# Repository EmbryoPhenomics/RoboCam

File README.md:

# RoboCam

## Robotic instrument for timelapse imaging in multiwell plate format

RoboCam is a compact, modular laboratory instrument, with robotic motion and built-in compute, it is capable of timelapse imaging of various multiwell plate formats. 

Some of the key specifications of this instruments are as follows:

| Component | Description |
|:---|:---|
| Robotic stage | Automated lead-screw driven XYZ stage with < 1 µm precision and < 10 µm repeatability. The stage is camera-driven rather than sample-driven, reducing vibration transmitted to samples. |
| Processors | Raspberry Pi 5 8Gb RAM computer with built-in fast NVME storage running Debian Linux. |
| Camera sensor | Two camera sensor options: Global shutter CMOS 1.58-megapixel (Sony IMX296LQR-C). Rolling shutter CMOS 12.3-megapixel (Sony IMX477R) |
| Video resolution | Global shutter: 1456x1088 60fps max. Rolling shutter: 1920x1080 50fps max. Higher resolution possible at reduced framerate. Resolution and framerate can be configured using built-in app. |
| Lens | Adjustable high magnification and low magnification lens included. Auxillary, stackable lenses (x2, x3, x4 and x6) provided for high magnification lens to achieve greater magnification. | 
| Lighting | Ring light consisting of 36 individually lit 3mm LEDs. Brightness can be configured and controlled through built-in app. |
| Configuration | Setup via Web App using built-in touchscreen, enabling live stream and config of camera sensor, positioning of XYZ stage and programming of experimental schedule. Experimental data can be captured to built-in disk or to USB attached storage. |
| Sensors | Compact, enclosed aluminium frame with damped door for access and panel cutouts for routing of auxiliary hardware. | 
| Dimensions | 325 mm x 442 mm x 510 mm |

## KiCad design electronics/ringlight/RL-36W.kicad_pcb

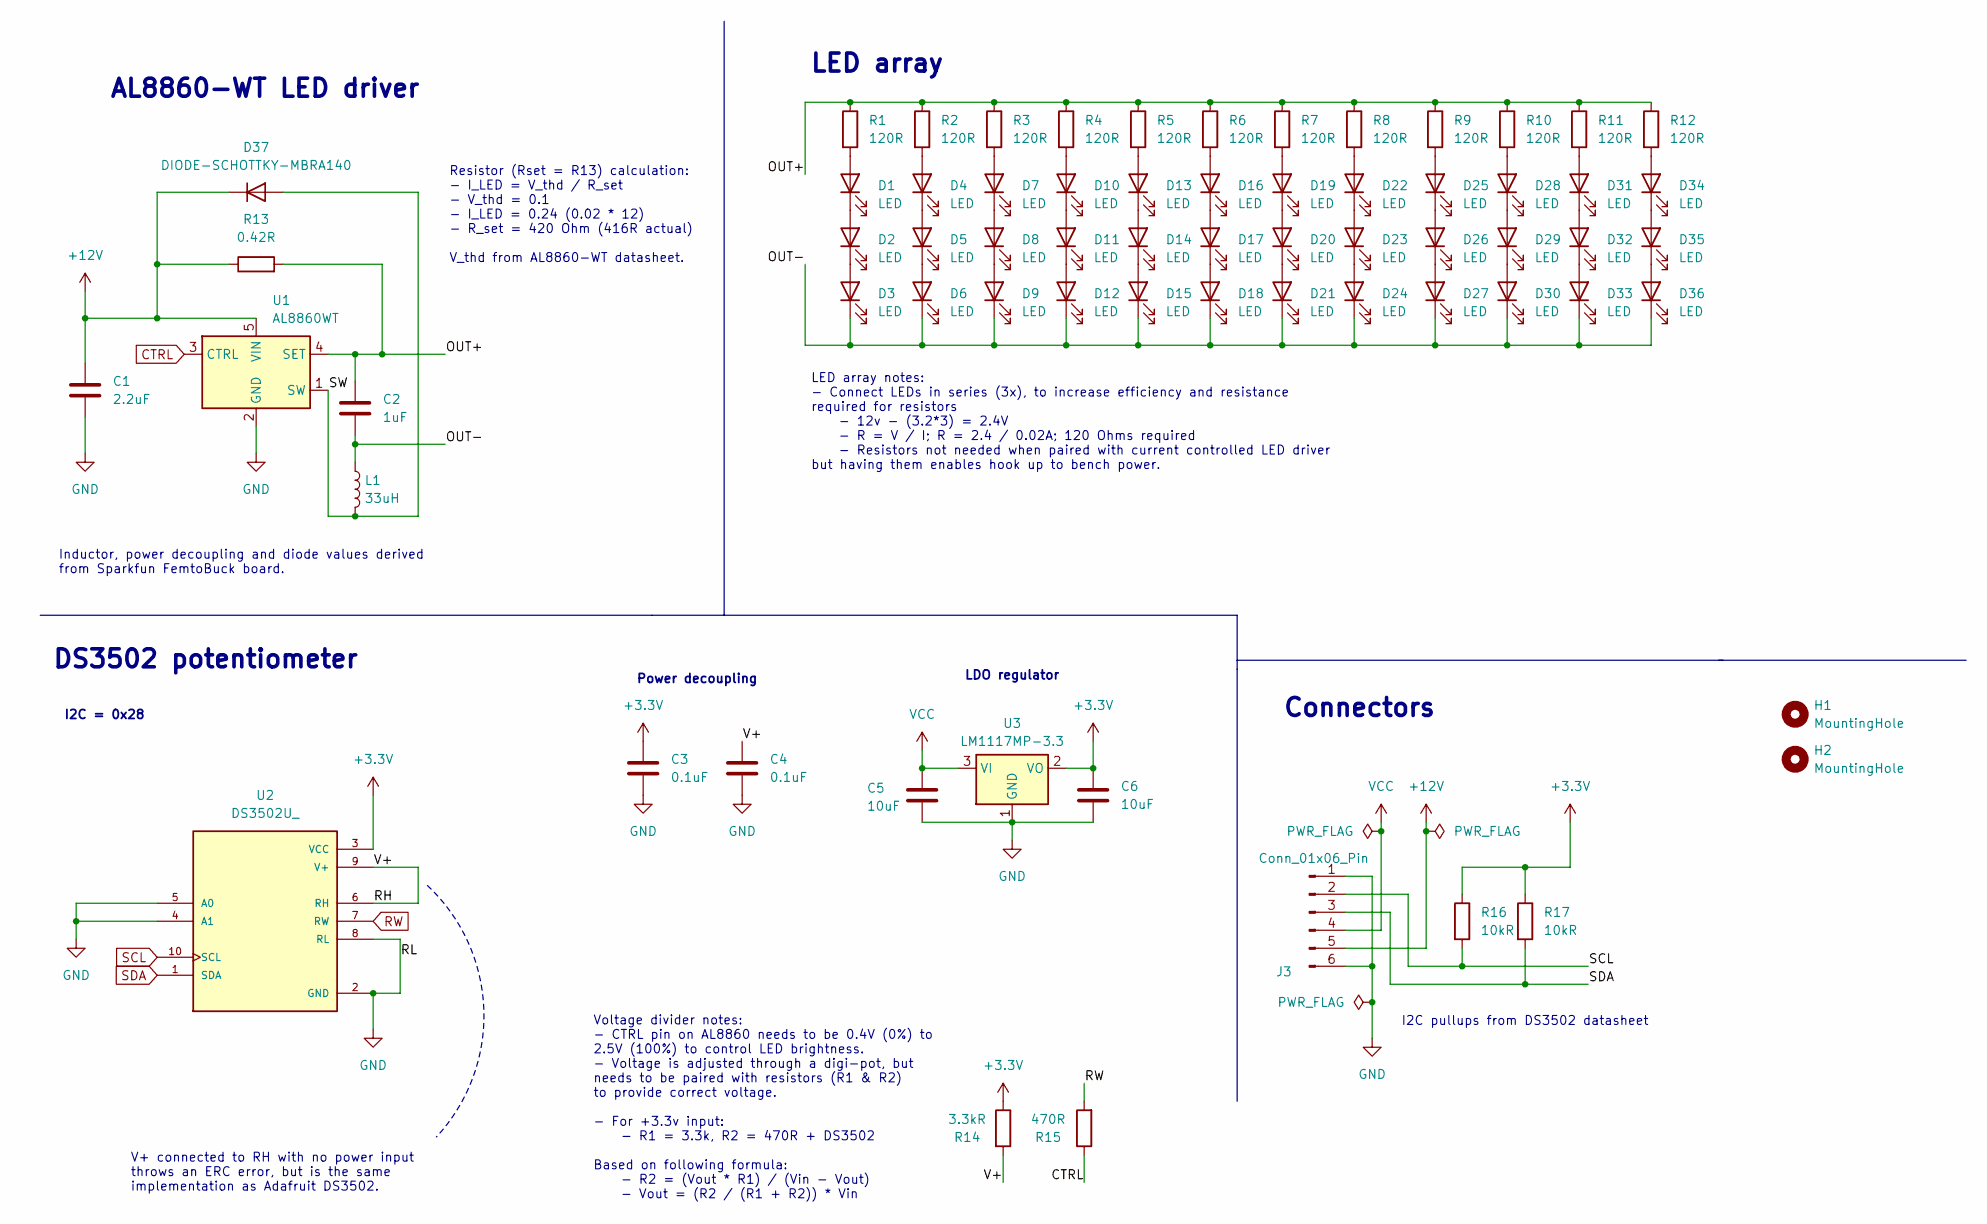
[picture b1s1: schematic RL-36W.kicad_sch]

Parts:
C1: 2.2uF; C_1206_3216Metric
C2: 1uF; C_1206_3216Metric
C3, C4: 0.1uF; C_0402_1005Metric
C5, C6: 10uF; C_1206_3216Metric
D1, D2, D3, D4, D5, D6, D7, D8, D9, D10, D11, D12, D13, D14, D15, D16, D17, D18, D19, D20, D21, D22, D23, D24, D25, D26, D27, D28, D29, D30, D31, D32, D33, D34, D35, D36: LED; LED_D3.0mm_2
D37: DIODE-SCHOTTKY-MBRA140; D_SMA
H1, H2: MountingHole; MountingHole_2mm
J3: Conn_01x06_Pin; JST_PH_S6B-PH-K_1x06_P2.00mm_Horizontal
L1: 33uH; L_Bourns_SRN6045TA
R1, R2, R3, R4, R5, R6, R7, R8, R9, R10, R11, R12: 120R; R_0402_1005Metric
R13: 0.42R; R_0603_1608Metric
R14: 3.3kR; R_0603_1608Metric
R15: 470R; R_0402_1005Metric
R16, R17: 10kR; R_0603_1608Metric
U1: AL8860WT; TSOT-23-5
U2: DS3502U_; SOP50P490X110-10N; PARTREV 1
U3: LM1117MP-3.3; SOT-223-3_TabPin2

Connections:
+3.3V: C3.1, C6.1, R14.1, R16.1, R17.1, U2.3 (VCC), U3.2 (VO)
+12V: C1.1, D37.1 (K), J3.5, R13.1, U1.5 (VIN)
/OUT+: C2.1, R1.1, R2.1, R3.1, R4.1, R5.1, R6.1, R7.1, R8.1, R9.1, R10.1, R11.1, R12.1, R13.2, U1.4 (SET)
/OUT-: C2.2, D3.1 (K), D6.1 (K), D9.1 (K), D12.1 (K), D15.1 (K), D18.1 (K), D21.1 (K), D24.1 (K), D27.1 (K), D30.1 (K), D33.1 (K), D36.1 (K), L1.1
/RH: C4.1, R14.2, U2.6 (RH), U2.9 (V+)
/SW: D37.2 (A), L1.2, U1.1 (SW)
CTRL: R15.1, U1.3 (CTRL)
GND: C1.2, C3.2, C4.2, C5.2, C6.2, J3.1, J3.6, U1.2 (GND), U2.2 (GND), U2.4 (A1), U2.5 (A0), U2.8 (RL), U3.1 (GND)
unnamed: D1.2 (A), R1.2
unnamed: D1.1 (K), D2.2 (A)
unnamed: D2.1 (K), D3.2 (A)
unnamed: D4.2 (A), R2.2
unnamed: D4.1 (K), D5.2 (A)
unnamed: D5.1 (K), D6.2 (A)
unnamed: D7.2 (A), R3.2
unnamed: D7.1 (K), D8.2 (A)
unnamed: D8.1 (K), D9.2 (A)
unnamed: D10.2 (A), R4.2
unnamed: D10.1 (K), D11.2 (A)
unnamed: D11.1 (K), D12.2 (A)
unnamed: D13.2 (A), R5.2
unnamed: D13.1 (K), D14.2 (A)
unnamed: D14.1 (K), D15.2 (A)
unnamed: D16.2 (A), R6.2
unnamed: D16.1 (K), D17.2 (A)
unnamed: D17.1 (K), D18.2 (A)
unnamed: D19.2 (A), R7.2
unnamed: D19.1 (K), D20.2 (A)
unnamed: D20.1 (K), D21.2 (A)
unnamed: D22.2 (A), R8.2
unnamed: D22.1 (K), D23.2 (A)
unnamed: D23.1 (K), D24.2 (A)
unnamed: D25.2 (A), R9.2
unnamed: D25.1 (K), D26.2 (A)
unnamed: D26.1 (K), D27.2 (A)
unnamed: D28.2 (A), R10.2
unnamed: D28.1 (K), D29.2 (A)
unnamed: D29.1 (K), D30.2 (A)
unnamed: D31.2 (A), R11.2
unnamed: D31.1 (K), D32.2 (A)
unnamed: D32.1 (K), D33.2 (A)
unnamed: D34.2 (A), R12.2
unnamed: D34.1 (K), D35.2 (A)
unnamed: D35.1 (K), D36.2 (A)
RW: R15.2, U2.7 (RW)
SCL: J3.2, R16.2, U2.10 (SCL)
SDA: J3.3, R17.2, U2.1 (SDA)
VCC: C5.1, J3.4, U3.3 (VI)

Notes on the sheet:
V+ connected to RH with no power input throws an ERC error, but is the same implementation as Adafruit DS3502.
I2C = 0x28
LED array notes: - Connect LEDs in series (3x), to increase efficiency and resistance required for resistors - 12v - (3.2*3) = 2.4V - R = V / I; R = 2.4 / 0.02A; 120 Ohms required - Resistors not needed when paired with current controlled LED driver but having them enables hook up to bench power.
Connectors
LED array
Resistor (Rset = R13) calculation: - I_LED = V_thd / R_set - V_thd = 0.1 - I_LED = 0.24 (0.02 * 12) - R_set = 420 Ohm (416R actual) V_thd from AL8860-WT datasheet.
Power decoupling
Inductor, power decoupling and diode values derived from Sparkfun FemtoBuck board.
DS3502 potentiometer
Voltage divider notes: - CTRL pin on AL8860 needs to be 0.4V (0%) to 2.5V (100%) to control LED brightness. - Voltage is adjusted through a digi-pot, but needs to be paired with resistors (R1 & R2) to provide correct voltage. - For +3.3v input: - R1 = 3.3k, R2 = 470R + DS3502 Based on following for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
LDO regulator
AL8860-WT LED driver
I2C pullups from DS3502 datasheet

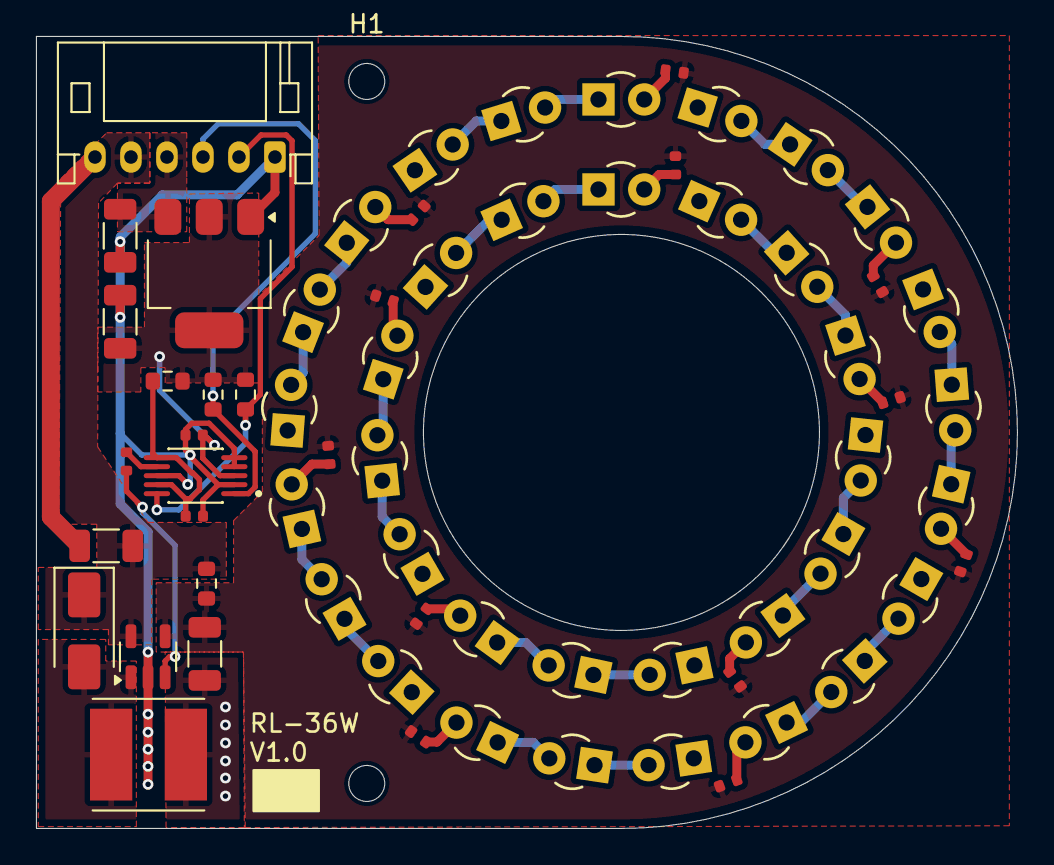
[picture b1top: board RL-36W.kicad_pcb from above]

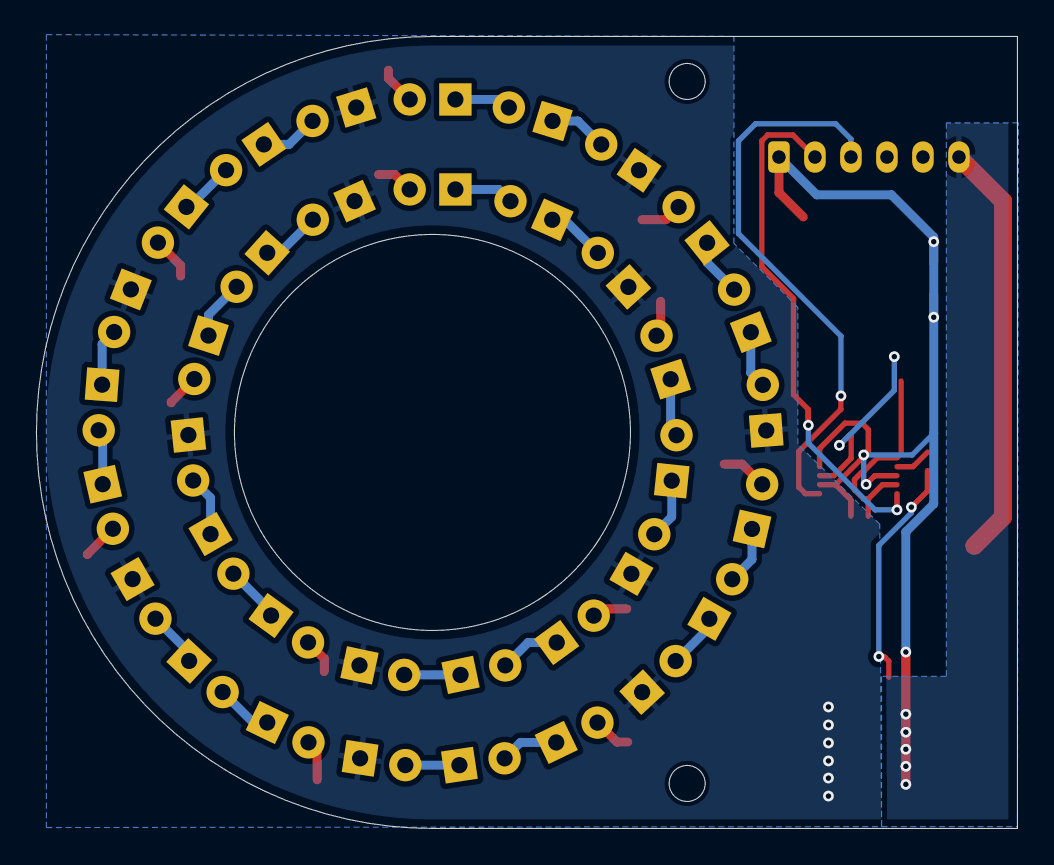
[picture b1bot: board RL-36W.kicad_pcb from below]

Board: 2 copper layers, 54.5 x 44.0 mm, 67 parts (36 on the bottom side), 48 nets.

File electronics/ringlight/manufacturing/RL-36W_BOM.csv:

Comment,Designator,Footprint,JLCPCB Part #,Notes,Correct?
2.2uF,C1,Capacitor_SMD:C_1206_3216Metric,C472849,,
1uF,C2,Capacitor_SMD:C_1206_3216Metric,C577248,,
0.1uF,"C3,C4",Capacitor_SMD:C_0402_1005Metric,C307331,,
10uF,"C5,C6",Capacitor_SMD:C_1206_3216Metric,C5141283,,
DIODE-SCHOTTKY-MBRA140,D37,Diode_SMD:D_SMA,C54798,,
33uH,L1,Inductor_SMD:L_Bourns_SRN6045TA,C780211,,
120R,"R1,R2,R3,R4,R5,R6,R7,R8,R9,R10,R11,R12",attempt_2:R_0402_1005Metric,C911631,,
0.42R,R13,Resistor_SMD:R_0603_1608Metric,C705494,,
3.3kR,R14,Resistor_SMD:R_0603_1608Metric,C5250825,,
470R,R15,Resistor_SMD:R_0402_1005Metric,C2689463,,
10kR,"R16,R17",Resistor_SMD:R_0603_1608Metric,C99198,,
AL8860WT,U1,Package_TO_SOT_SMD:TSOT-23-5,C125330,,
DS3502U_,U2,attempt_2:SOP50P490X110-10N,C2649363,,
LM1117MP-3.3,U3,Package_TO_SOT_SMD:SOT-223-3_TabPin2,C9662,,

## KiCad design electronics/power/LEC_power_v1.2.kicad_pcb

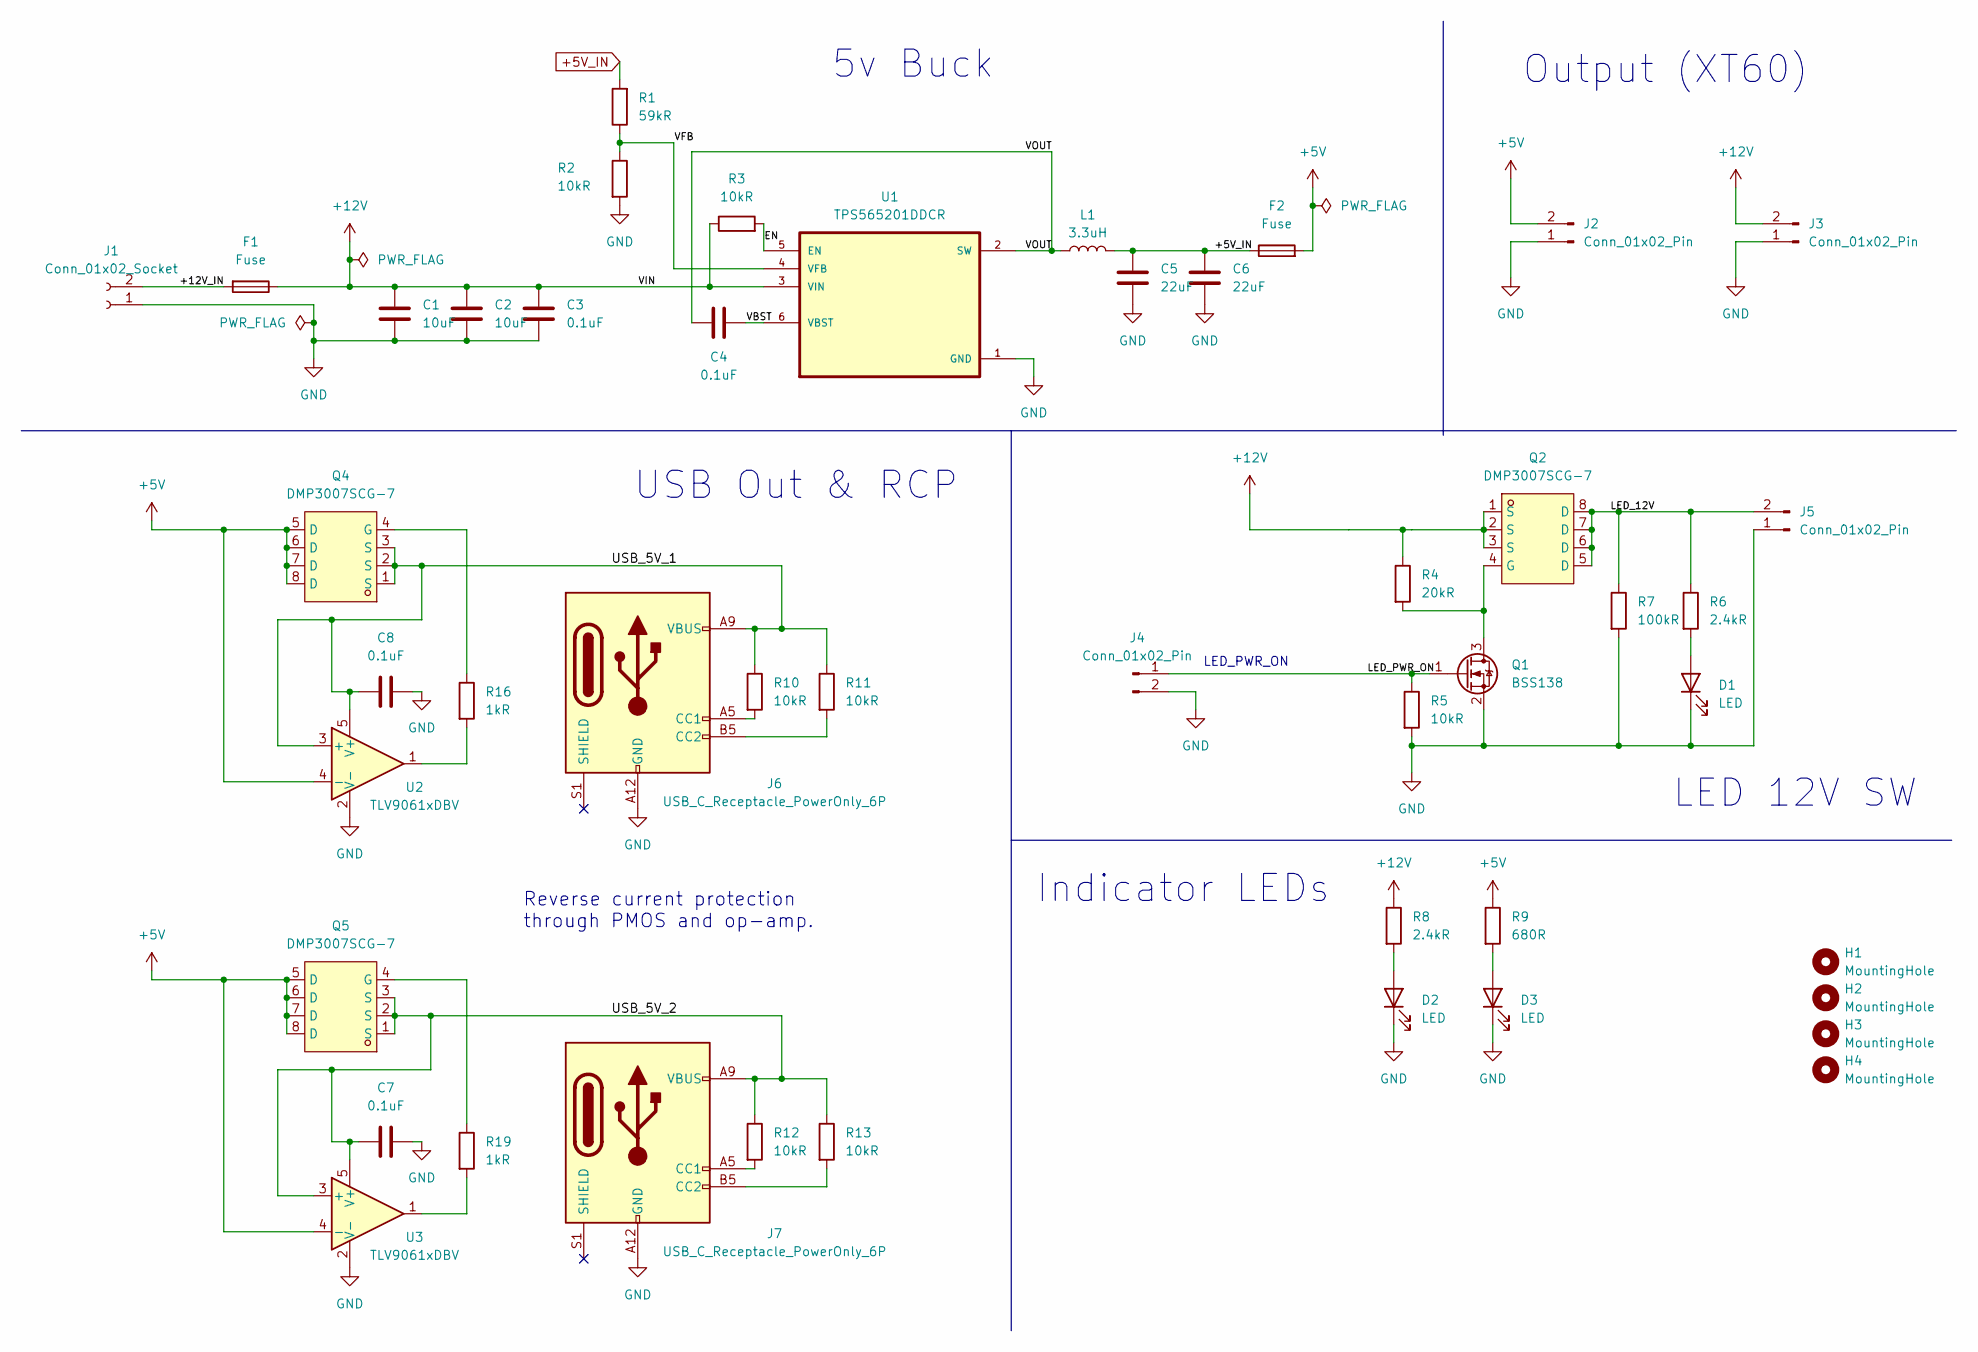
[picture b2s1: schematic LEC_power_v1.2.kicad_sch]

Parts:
C1, C2: 10uF; C_0805_2012Metric
C3, C4, C7, C8: 0.1uF; C_0603_1608Metric
C5, C6: 22uF; C_1206_3216Metric
D1, D2, D3: LED; LED_0603_1608Metric
F1, F2: Fuse; CamdenBoss_FuseHolder_5x20mm
H1, H2, H3, H4: MountingHole; MountingHole_3.2mm_M3
J1: Conn_01x02_Socket; AMASS_XT60PW-M_1x02_P7.20mm_Horizontal
J2, J3: Conn_01x02_Pin; AMASS_XT60PW-F_1x02_P7.20mm_Horizontal
J4: Conn_01x02_Pin; JST_PH_S2B-PH-K_1x02_P2.00mm_Horizontal
J5: Conn_01x02_Pin; JST_XH_S2B-XH-A_1x02_P2.50mm_Horizontal
J6, J7: USB_C_Receptacle_PowerOnly_6P; USB_C_Receptacle_GCT_USB4125-xx-x-0190_6P_TopMnt_Horizontal
L1: 3.3uH; L_Coilcraft_XAL7070-XXX
Q1: BSS138; SOT-23
Q2, Q4, Q5: DMP3007SCG-7; V-DFN3333-8_L3.3-W3.3-P0.65-BL; LCSC Part C260899
R1: 59kR; R_0603_1608Metric
R2, R3, R5, R10, R11, R12, R13: 10kR; R_0603_1608Metric
R4: 20kR; R_0603_1608Metric
R6, R8: 2.4kR; R_0603_1608Metric
R7: 100kR; R_0603_1608Metric
R9: 680R; R_0603_1608Metric
R16, R19: 1kR; R_0603_1608Metric
U1: TPS565201DDCR; SOT95P280X110-6N
U2, U3: TLV9061xDBV; SOT-23-5

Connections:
+5V: F2.2, J2.2, Q4.5 (D), Q4.6 (D), Q4.7 (D), Q4.8 (D), Q5.5 (D), Q5.6 (D), Q5.7 (D), Q5.8 (D), R9.1, U2.4 (-), U3.4 (-)
+5V_IN: C5.1, C6.1, F2.1, L1.2, R1.2
+12V: C1.1, C2.1, C3.1, F1.1, J3.2, Q2.1 (S), Q2.2 (S), Q2.3 (S), R3.1, R4.1, R8.1, U1.3 (VIN)
/+12V_IN: F1.2, J1.2
/EN: R3.2, U1.5 (EN)
/LED_12V: J5.2, Q2.5 (D), Q2.6 (D), Q2.7 (D), Q2.8 (D), R6.1, R7.1
/LED_PWR_ON: J4.1, Q1.1 (G), R5.1
/USB_5V_1: C8.1, J6.A9 (VBUS), J6.B9 (VBUS), Q4.1 (S), Q4.2 (S), Q4.3 (S), R10.1, R11.1, U2.3 (+), U2.5 (V+)
/USB_5V_2: C7.1, J7.A9 (VBUS), J7.B9 (VBUS), Q5.1 (S), Q5.2 (S), Q5.3 (S), R12.1, R13.1, U3.3 (+), U3.5 (V+)
/VBST: C4.1, U1.6 (VBST)
/VFB: R1.1, R2.1, U1.4 (VFB)
/VOUT: C4.2, L1.1, U1.2 (SW)
GND: C1.2, C2.2, C3.2, C5.2, C6.2, C7.2, C8.2, D1.1 (K), D2.1 (K), D3.1 (K), J1.1, J2.1, J3.1, J4.2, J5.1, J6.A12 (GND), J6.B12 (GND), J7.A12 (GND), J7.B12 (GND), Q1.2 (S), R2.2, R5.2, R7.2, U1.1 (GND), U2.2 (V-), U3.2 (V-)
unnamed: D1.2 (A), R6.2
unnamed: D2.2 (A), R8.2
unnamed: D3.2 (A), R9.2
unnamed: J6.A5 (CC1), R10.2
unnamed: J6.B5 (CC2), R11.2
unnamed: J7.A5 (CC1), R12.2
unnamed: J7.B5 (CC2), R13.2
unnamed: Q1.3 (D), Q2.4 (G), R4.2
unnamed: Q4.4 (G), R16.1
unnamed: Q5.4 (G), R19.1
unnamed: R16.2, U2.1
unnamed: R19.2, U3.1

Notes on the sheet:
5v Buck
USB Out & RCP
Reverse current protection through PMOS and op-amp.
LED_PWR_ON
LED 12V SW
Output (XT60)
Indicator LEDs

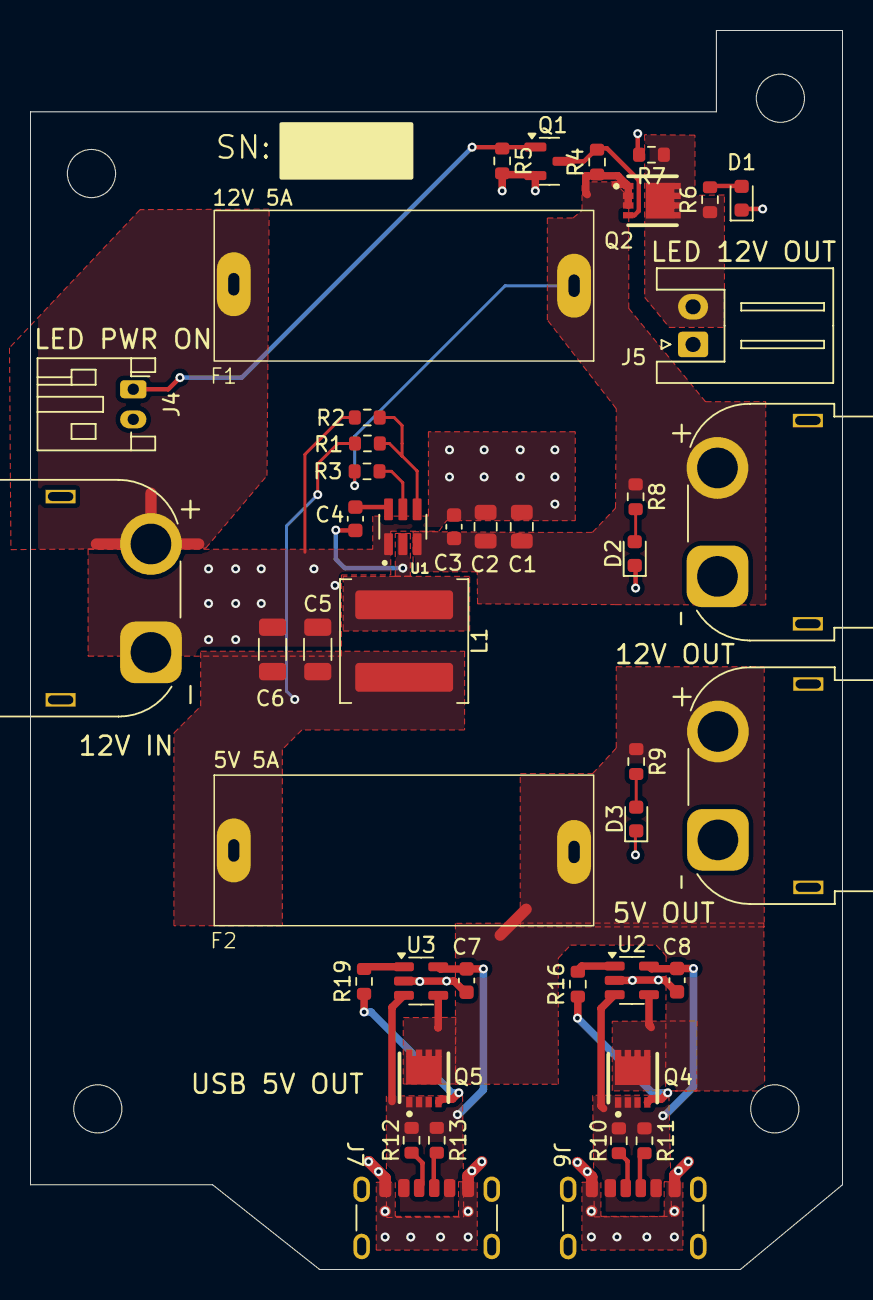
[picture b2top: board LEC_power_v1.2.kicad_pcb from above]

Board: 2 copper layers, 53.9 x 82.3 mm, 47 parts (0 on the bottom side), 25 nets.

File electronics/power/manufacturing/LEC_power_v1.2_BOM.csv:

Comment,Designator,Footprint,JLCPCB Part #（optional）
10uF,"C1,C2",Capacitor_SMD:C_0805_2012Metric,C440198
0.1uF,"C3,C4,C7,C8",Capacitor_SMD:C_0603_1608Metric,C14663
22uF,"C5,C6",Capacitor_SMD:C_1206_3216Metric,C12891
LED,"D1,D2,D3",LED_SMD:LED_0603_1608Metric,C511604
USB_C_Receptacle_PowerOnly_6P,"J6,J7",Connector_USB:USB_C_Receptacle_GCT_USB4125-xx-x-0190_6P_TopMnt_Horizontal,C456012
3.3uH,L1,Inductor_SMD:L_Coilcraft_XAL7070-XXX,C3911435
BSS138,Q1,Package_TO_SOT_SMD:SOT-23,C82045
DMP3007SCG-7,"Q2,Q4,Q5",jlcpcb:V-DFN3333-8_L3.3-W3.3-P0.65-BL,C260899
59kR,R1,Resistor_SMD:R_0603_1608Metric,C309564
10kR,"R2,R3,R5,R10,R11,R12,R13",Resistor_SMD:R_0603_1608Metric,C98220
20kR,R4,Resistor_SMD:R_0805_2012Metric,C4328
2.4kR,"R6,R8",Resistor_SMD:R_0603_1608Metric,C22940
100kR,R7,Resistor_SMD:R_0805_2012Metric,C149504
680R,R9,Resistor_SMD:R_0603_1608Metric,C23228
1kR,"R16,R19",Resistor_SMD:R_0805_2012Metric,C17513
TPS565201DDCR,U1,jlcpcb:SOT95P280X110-6N,C327676
TLV9061xDBV,"U2,U3",Package_TO_SOT_SMD:SOT-23-5,C398358
